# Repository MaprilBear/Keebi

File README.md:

# Keebi

Final project of ECE 445L (Embedded Systems Design Lab) at UT Austin with Mark McDermott (Fall 2023)

The Keebi is a USB and Bluetooth enabled wireless hotswappable 60% keyboard with an attached color TFT LCD

MCUs: TM4C123G and the BGM220P <br>
LCD: Adafruit 1.8" TFT LCD (Product ID 358) <br>

A bill of materials is included in this repository

## Credits
- April Douglas - Schematic and PCB Design, Firmware
- Matija Jankovic - Schematic and PCB Design, PCB Assembly
- Jenna May - Firmware
- Eric Wang - Case

## How to Use
- Fn+B - Toggle Bluetooth 
- Fn+Period - Cycle between apps 
- All keys are defined in Switch_Matrix.c

## Errata
1.  The bottom row of keys is unconnected to the main MCU
    -  Fix - Solder a wire from the bottom of the Left Arrow key diode to the TDO pin of the JTAG pinout. Holding down both shift keys will return TDO to it's JTAG confirguration and allow for flashing
2. There is crosstalk between the control, alt, shift, and windows keys in the bottom right. Win+RShift for example is detected as Ctrl+Win+RShift and Ctrl+Z is sometimes detected as Ctrl+Alt+Z
    - No Fix 
3. Bluetooth will sometimes break and cause the keyboard to become entirely unresponsive outside of the current app on the display
    - Workaround - When using bluetooth make sure to toggle the blank screen app with Fn+Period, this will avoid the crash in most situations
    - Theorized Cause - Crosstalk between LCD SPI traces and UART traces to the BGM220P or some other issue leading to malformed UART packets which the BGM220P firmware is not designed to handle

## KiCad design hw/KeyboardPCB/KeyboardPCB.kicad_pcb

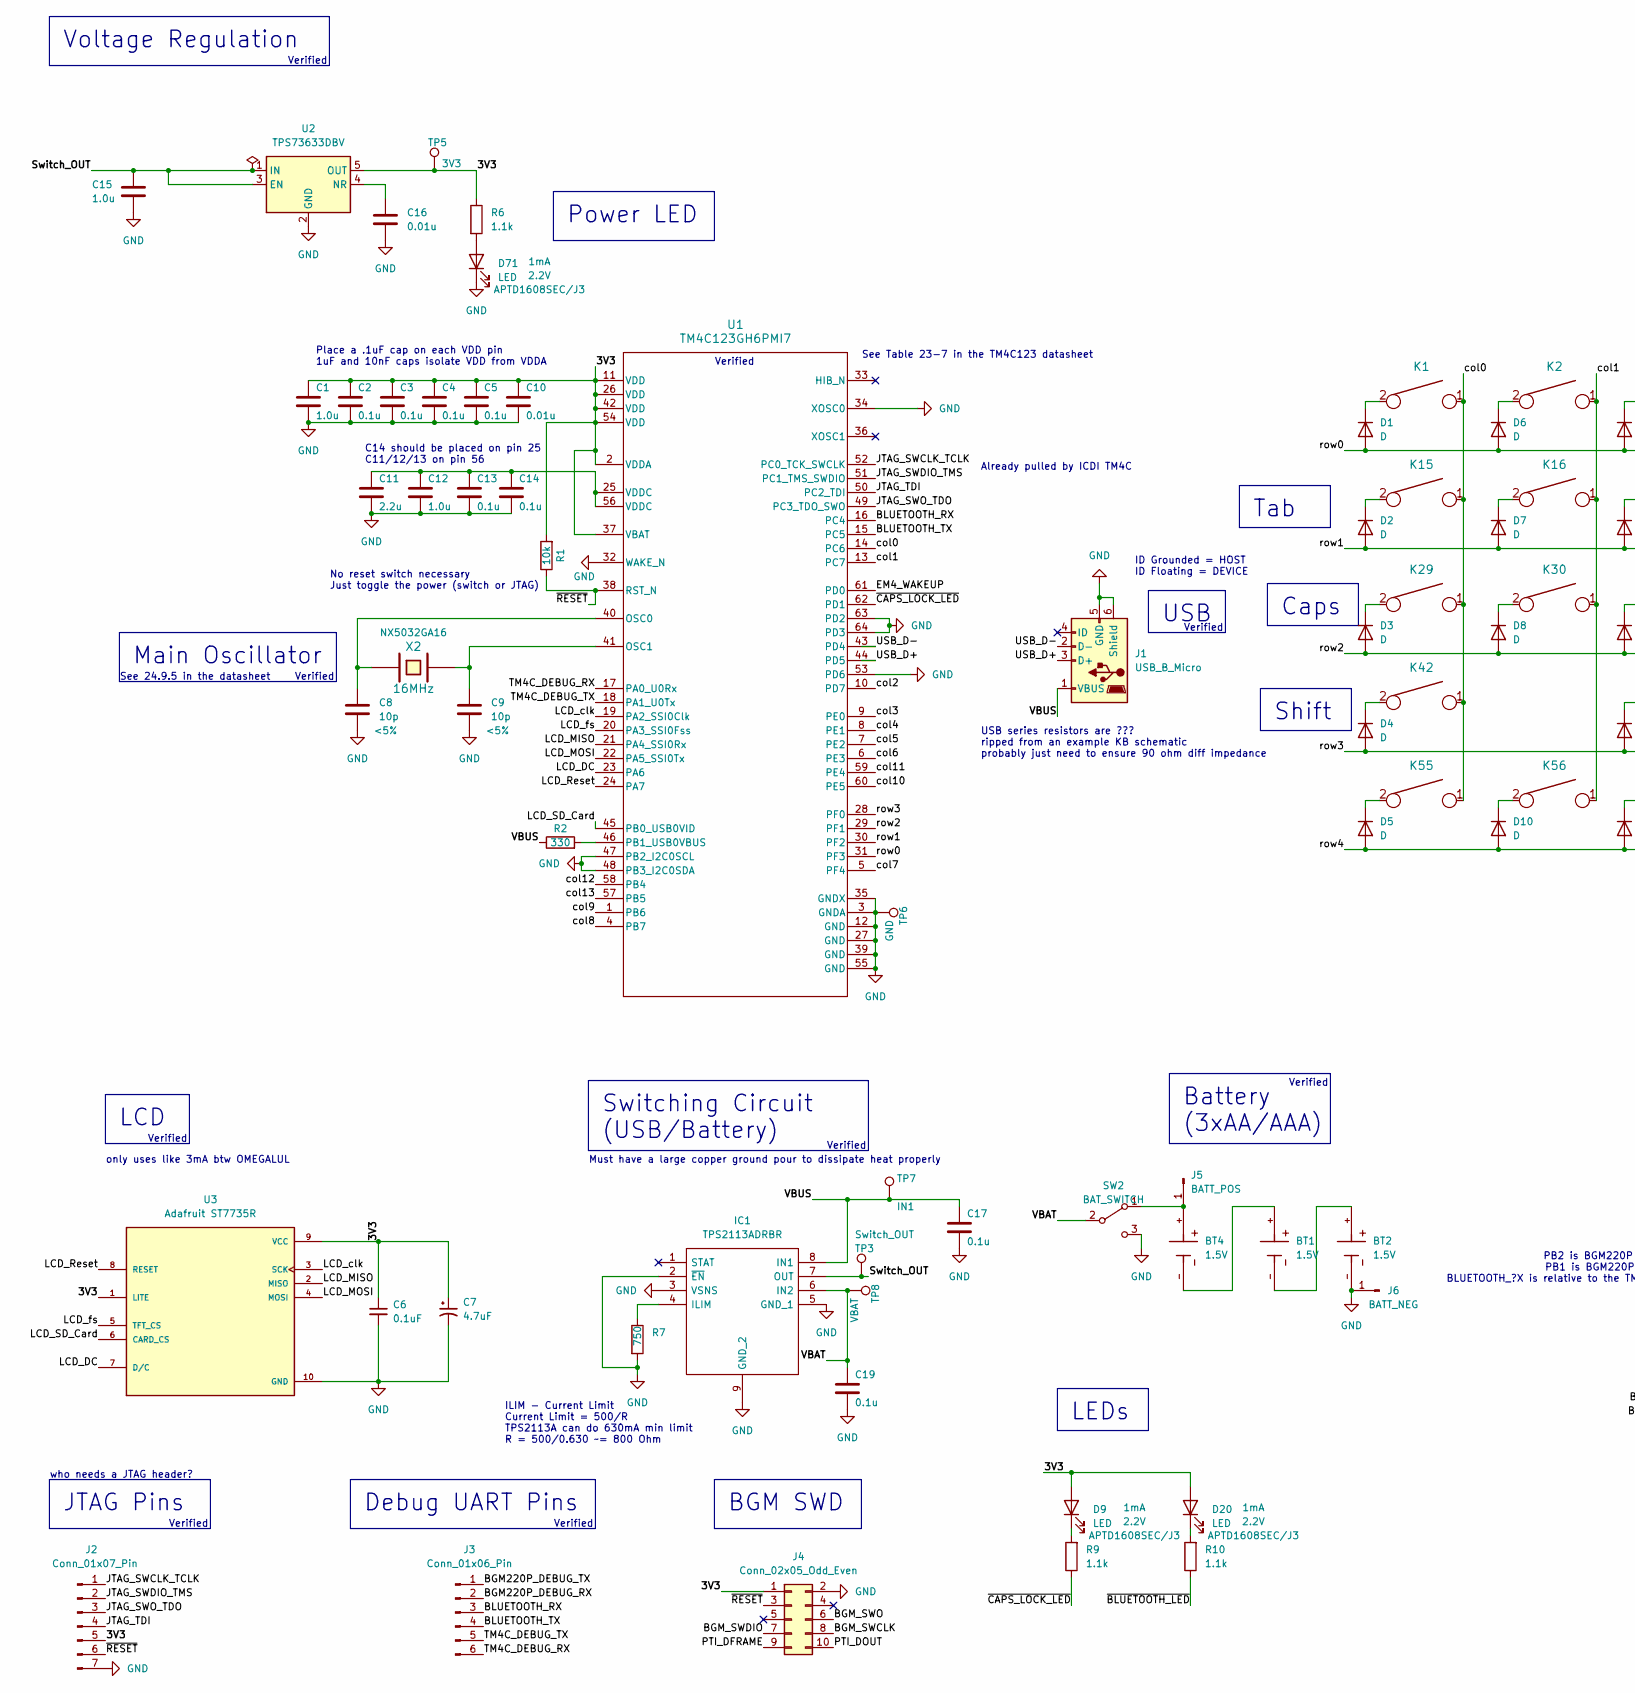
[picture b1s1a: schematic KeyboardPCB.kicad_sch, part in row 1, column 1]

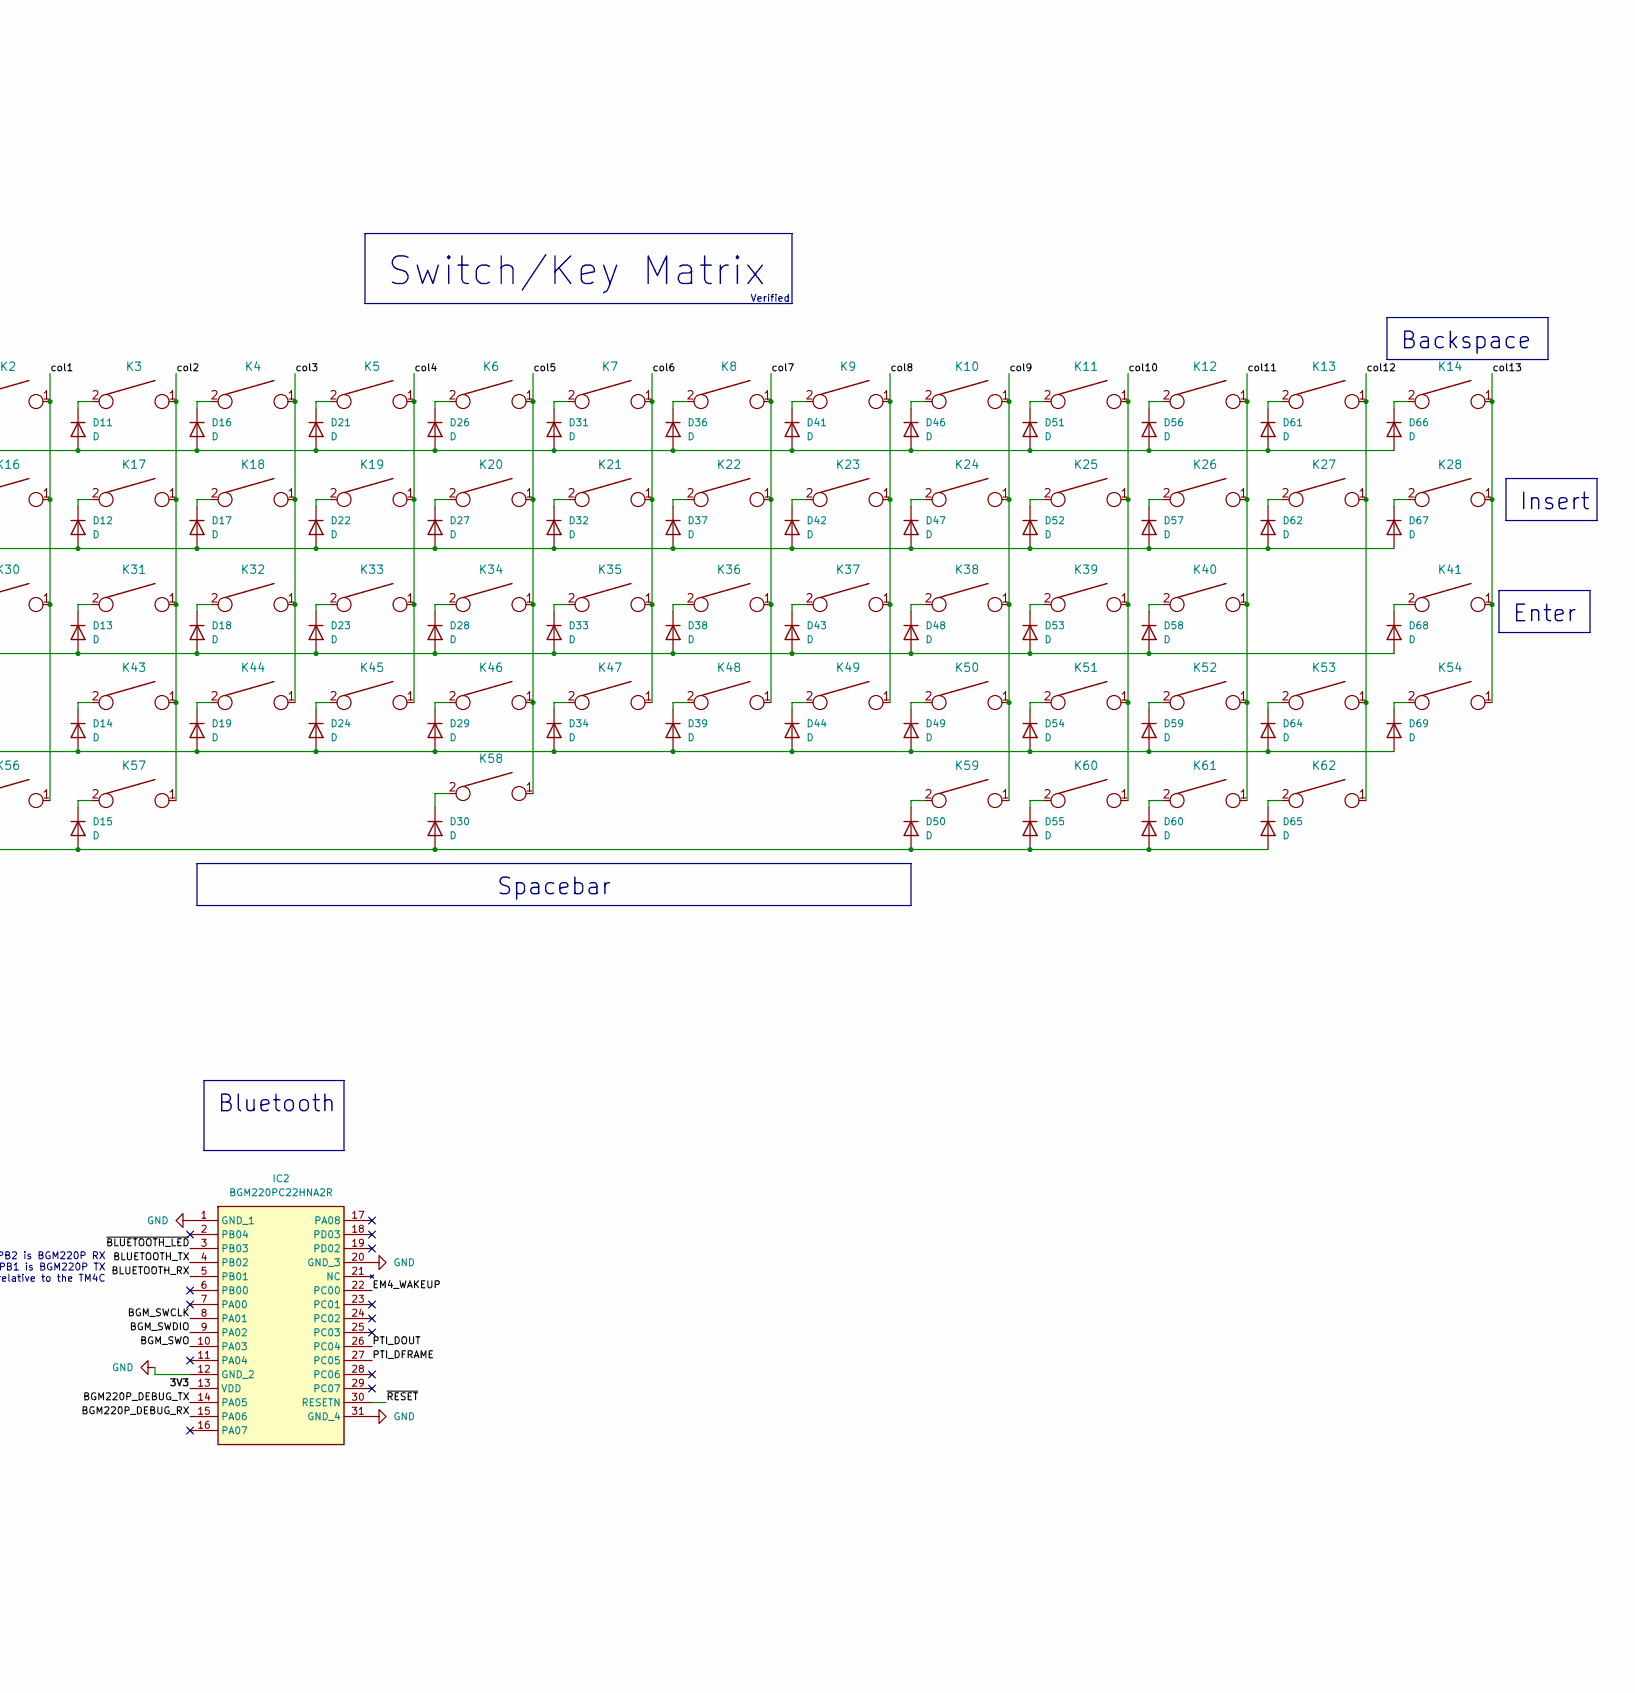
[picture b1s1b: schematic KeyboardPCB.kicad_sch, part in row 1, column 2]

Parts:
BT1, BT2, BT4: 1.5V; PARTREV A
C1, C12, C15: 1.0u; C_0603_1608Metric_Pad1.08x0.95mm_HandSolder
C2, C3, C4, C5, C13, C14, C17, C19: 0.1u; C_0603_1608Metric_Pad1.08x0.95mm_HandSolder
C6: 0.1uF; C_0603_1608Metric_Pad1.08x0.95mm_HandSolder
C7: 4.7uF; C_0603_1608Metric_Pad1.08x0.95mm_HandSolder
C8, C9: 10p; C_0603_1608Metric_Pad1.08x0.95mm_HandSolder; Tolerance <5%
C10, C16: 0.01u; C_0603_1608Metric_Pad1.08x0.95mm_HandSolder
C11: 2.2u; C_0603_1608Metric_Pad1.08x0.95mm_HandSolder
D1, D2, D3, D4, D5, D6, D7, D8, D10, D11, D12, D13, D14, D15, D16, D17, D18, D19, D21, D22, D23, D24, D26, D27, D28, D29, D30, D31, D32, D33, D34, D36, D37, D38, D39, D41, D42, D43, D44, D46, D47, D48, D49, D50, D51, D52, D53, D54, D55, D56, D57, D58, D59, D60, D61, D62, D64, D65, D66, D67, D68, D69: D; D_SOD-123
D9, D20, D71: LED; LED_0603_1608Metric_Pad1.05x0.95mm_HandSolder; Part APTD1608SEC/J3
IC1: TPS2113ADRBR; SON65P300X300X100-9N-D; Mouser Part Number 595-TPS2113ADRBR
IC2: BGM220PC22HNA2R; Mouser Part Number 634-BGM220PC22HNA2R
J1: USB_B_Micro; USB_Micro-B_Amphenol_10103594-0001LF_Horizontal
J2: Conn_01x07_Pin; PinHeader_1x07_P2.54mm_Vertical
J3: Conn_01x06_Pin; PinHeader_1x06_P2.54mm_Vertical
J4: Conn_02x05_Odd_Even; PinHeader_2x05_P1.27mm_Vertical
J5: BATT_POS; Pin_D1.0mm_L10.0mm
J6: BATT_NEG; Pin_D1.0mm_L10.0mm
K1, K2, K3, K4, K5, K6, K7, K8, K9, K10, K11, K12, K13, K16, K17, K18, K19, K20, K21, K22, K23, K24, K25, K26, K27, K30, K31, K32, K33, K34, K35, K36, K37, K38, K39, K40, K43, K44, K45, K46, K47, K48, K49, K50, K51, K52: KEYSW; MX-Hotswap-1U
K14: KEYSW; MX-Hotswap-2U
K15, K28, K53: KEYSW; MX-Hotswap-1.5U
K29: KEYSW; MX-Hotswap-1.75U
K41, K42: KEYSW; MX-Hotswap-2.25U
K54, K55, K56, K57, K59, K60, K61, K62: KEYSW; MX-Hotswap-1.25U
K58: KEYSW; MX-Hotswap-6.25U
R1: 10k; R_0402_1005Metric
R2: 330; R_0402_1005Metric
R6, R9, R10: 1.1k; R_0402_1005Metric
R7: 750; R_0402_1005Metric
SW2: BAT_SWITCH; SLW1215865AD
TP3: Switch_OUT; TestPoint_Pad_2.5x2.5mm
TP5: 3V3; TestPoint_Pad_2.5x2.5mm
TP6: GND; TestPoint_Pad_2.5x2.5mm
TP7: IN1; TestPoint_Pad_2.5x2.5mm
TP8: VBAT; TestPoint_Pad_2.5x2.5mm
U1: TM4C123GH6PMI7; QFP50P1200X1200X160-64N
U2: TPS73633DBV; SOT-23-5
U3: Adafruit ST7735R; adafruit_st7735r
X2: 16MHz; NX5032GA16000000MHZLNCD1

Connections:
/3V3: C1.1, C2.1, C3.1, C4.1, C5.1, C6.1, C7.1, C10.1, D9.2 (A), D20.2 (A), IC2.13 (VDD), J2.5, J4.1, R1.2, R6.1, TP5.1, U1.2 (VDDA), U1.11 (VDD), U1.26 (VDD), U1.37 (VBAT), U1.42 (VDD), U1.54 (VDD), U2.5 (OUT), U3.1 (LITE), U3.9 (VCC)
/BGM220P_DEBUG_RX: IC2.15 (PA06), J3.2
/BGM220P_DEBUG_TX: IC2.14 (PA05), J3.1
/BGM_SWCLK: IC2.8 (PA01), J4.8
/BGM_SWDIO: IC2.9 (PA02), J4.7
/BGM_SWO: IC2.10 (PA03), J4.6
/BLUETOOTH_RX: IC2.5 (PB01), J3.3, U1.16 (PC4)
/BLUETOOTH_TX: IC2.4 (PB02), J3.4, U1.15 (PC5)
/EM4_WAKEUP: IC2.22 (PC00), U1.61 (PD0)
/JTAG_SWCLK_TCLK: J2.1, U1.52 (PC0_TCK_SWCLK)
/JTAG_SWDIO_TMS: J2.2, U1.51 (PC1_TMS_SWDIO)
/JTAG_SWO_TDO: J2.3, U1.49 (PC3_TDO_SWO)
/JTAG_TDI: J2.4, U1.50 (PC2_TDI)
/LCD_DC: U1.23 (PA6), U3.7 (D/C)
/LCD_MISO: U1.21 (PA4_SSI0Rx), U3.2 (MISO)
/LCD_MOSI: U1.22 (PA5_SSI0Tx), U3.4 (MOSI)
/LCD_Reset: U1.24 (PA7), U3.8 (RESET)
/LCD_SD_Card: U1.45 (PB0_USB0VID), U3.6 (CARD_CS)
/LCD_clk: U1.19 (PA2_SSI0Clk), U3.3 (SCK)
/LCD_fs: U1.20 (PA3_SSI0Fss), U3.5 (TFT_CS)
/PTI_DFRAME: IC2.27 (PC05), J4.9
/PTI_DOUT: IC2.26 (PC04), J4.10
/Switch_OUT: C15.2, IC1.7 (OUT), TP3.1, U2.1 (IN), U2.3 (EN)
/TM4C_DEBUG_RX: J3.6, U1.17 (PA0_U0Rx)
/TM4C_DEBUG_TX: J3.5, U1.18 (PA1_U0Tx)
/USB_D+: J1.3 (D+), U1.44 (PD5)
/USB_D-: J1.2 (D-), U1.43 (PD4)
/VBAT: C19.1, IC1.6 (IN2), SW2.2 (B), TP8.1
/VBUS: C17.1, IC1.8 (IN1), J1.1 (VBUS), R2.1, TP7.1
/col0: K1.1, K15.1, K29.1, K42.1, K55.1, U1.14 (PC6)
/col1: K2.1, K16.1, K30.1, K56.1, U1.13 (PC7)
/col2: K3.1, K17.1, K31.1, K43.1, K57.1, U1.10 (PD7)
/col3: K4.1, K18.1, K32.1, K44.1, U1.9 (PE0)
/col4: K5.1, K19.1, K33.1, K45.1, U1.8 (PE1)
/col5: K6.1, K20.1, K34.1, K46.1, K58.1, U1.7 (PE2)
/col6: K7.1, K21.1, K35.1, K47.1, U1.6 (PE3)
/col7: K8.1, K22.1, K36.1, K48.1, U1.5 (PF4)
/col8: K9.1, K23.1, K37.1, K49.1, U1.4 (PB7)
/col9: K10.1, K24.1, K38.1, K50.1, K59.1, U1.1 (PB6)
/col10: K11.1, K25.1, K39.1, K51.1, K60.1, U1.60 (PE5)
/col11: K12.1, K26.1, K40.1, K52.1, K61.1, U1.59 (PE4)
/col12: K13.1, K27.1, K53.1, K62.1, U1.58 (PB4)
/col13: K14.1, K28.1, K41.1, K54.1, U1.57 (PB5)
/row0: D1.2 (A), D6.2 (A), D11.2 (A), D16.2 (A), D21.2 (A), D26.2 (A), D31.2 (A), D36.2 (A), D41.2 (A), D46.2 (A), D51.2 (A), D56.2 (A), D61.2 (A), D66.2 (A), U1.31 (PF3)
/row1: D2.2 (A), D7.2 (A), D12.2 (A), D17.2 (A), D22.2 (A), D27.2 (A), D32.2 (A), D37.2 (A), D42.2 (A), D47.2 (A), D52.2 (A), D57.2 (A), D62.2 (A), D67.2 (A), U1.30 (PF2)
/row2: D3.2 (A), D8.2 (A), D13.2 (A), D18.2 (A), D23.2 (A), D28.2 (A), D33.2 (A), D38.2 (A), D43.2 (A), D48.2 (A), D53.2 (A), D58.2 (A), D68.2 (A), U1.29 (PF1)
/row3: D4.2 (A), D14.2 (A), D19.2 (A), D24.2 (A), D29.2 (A), D34.2 (A), D39.2 (A), D44.2 (A), D49.2 (A), D54.2 (A), D59.2 (A), D64.2 (A), D69.2 (A), U1.28 (PF0)
/row4: D5.2 (A), D10.2 (A), D15.2 (A), D30.2 (A), D50.2 (A), D55.2 (A), D60.2 (A), D65.2 (A)
/~BLUETOOTH_LED: IC2.3 (PB03), R10.1
/~CAPS_LOCK_LED: R9.1, U1.62 (PD1)
/~RESET: IC2.30 (RESETN), J2.6, J4.3, R1.1, U1.38 (RST_N)
GND: BT2.-, C1.2, C2.2, C3.2, C4.2, C5.2, C6.2, C7.2, C8.2, C9.2, C10.2, C11.2, C12.2, C13.2, C14.2, C15.1, C16.2, C17.2, C19.2, D71.1 (K), IC1.2 (~EN), IC1.3 (VSNS), IC1.5 (GND_1), IC1.9 (GND_2), IC2.1 (GND_1), IC2.12 (GND_2), IC2.20 (GND_3), IC2.31 (GND_4), J1.5 (GND), J1.6 (Shield), J2.7, J4.2, J6.1, R7.2, SW2.3 (C), TP6.1, U1.3 (GNDA), U1.12 (GND), U1.27 (GND), U1.32 (WAKE_N), U1.34 (XOSC0), U1.35 (GNDX), U1.39 (GND), U1.47 (PB2_I2C0SCL), U1.48 (PB3_I2C0SDA), U1.53 (PD6), U1.55 (GND), U1.63 (PD2), U1.64 (PD3), U2.2 (GND), U3.10 (GND)
unnamed: BT1.+, BT4.-
unnamed: BT1.-, BT2.+
unnamed: C11.1, C12.1, C13.1, C14.1, U1.25 (VDDC), U1.56 (VDDC)
unnamed: D1.1 (K), K1.2
unnamed: D2.1 (K), K15.2
unnamed: D3.1 (K), K29.2
unnamed: D4.1 (K), K42.2
unnamed: D5.1 (K), K55.2
unnamed: D6.1 (K), K2.2
unnamed: D7.1 (K), K16.2
unnamed: D8.1 (K), K30.2
unnamed: D9.1 (K), R9.2
unnamed: D10.1 (K), K56.2
unnamed: D11.1 (K), K3.2
unnamed: D12.1 (K), K17.2
unnamed: D13.1 (K), K31.2
unnamed: D14.1 (K), K43.2
unnamed: D15.1 (K), K57.2
unnamed: D16.1 (K), K4.2
unnamed: D17.1 (K), K18.2
unnamed: D18.1 (K), K32.2
unnamed: D19.1 (K), K44.2
unnamed: D20.1 (K), R10.2
unnamed: D21.1 (K), K5.2
unnamed: D22.1 (K), K19.2
unnamed: D23.1 (K), K33.2
unnamed: D24.1 (K), K45.2
unnamed: D26.1 (K), K6.2
unnamed: D27.1 (K), K20.2
unnamed: D28.1 (K), K34.2
unnamed: D29.1 (K), K46.2
unnamed: D30.1 (K), K58.2
unnamed: D31.1 (K), K7.2
unnamed: D32.1 (K), K21.2
unnamed: D33.1 (K), K35.2
unnamed: D34.1 (K), K47.2
unnamed: D36.1 (K), K8.2
unnamed: D37.1 (K), K22.2
unnamed: D38.1 (K), K36.2
unnamed: D39.1 (K), K48.2
unnamed: D41.1 (K), K9.2
unnamed: D42.1 (K), K23.2
unnamed: D43.1 (K), K37.2
unnamed: D44.1 (K), K49.2
unnamed: D46.1 (K), K10.2
unnamed: D47.1 (K), K24.2
unnamed: D48.1 (K), K38.2
unnamed: D49.1 (K), K50.2
unnamed: D50.1 (K), K59.2
unnamed: D51.1 (K), K11.2
unnamed: D52.1 (K), K25.2
unnamed: D53.1 (K), K39.2
unnamed: D54.1 (K), K51.2
unnamed: D55.1 (K), K60.2
unnamed: D56.1 (K), K12.2
unnamed: D57.1 (K), K26.2
unnamed: D58.1 (K), K40.2
unnamed: D59.1 (K), K52.2
unnamed: D60.1 (K), K61.2
unnamed: D61.1 (K), K13.2
unnamed: D62.1 (K), K27.2
unnamed: D64.1 (K), K53.2
unnamed: D65.1 (K), K62.2
unnamed: D66.1 (K), K14.2
unnamed: D67.1 (K), K28.2
unnamed: D68.1 (K), K41.2
unnamed: D69.1 (K), K54.2
unnamed: D71.2 (A), R6.2
unnamed: IC1.4 (ILIM), R7.1
unnamed: BT4.+, J5.1, SW2.1 (A)
unnamed: C8.1, U1.40 (OSC0), X2.1
unnamed: C9.1, U1.41 (OSC1), X2.2
unnamed: R2.2, U1.46 (PB1_USB0VBUS)
unnamed: C16.1, U2.4 (NR)

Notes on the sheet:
Shift
Main Oscillator
Caps
JTAG Pins
Bluetooth
USB
LCD
Insert
Voltage Regulation
Backspace
Switch/Key Matrix
Tab
Enter
BGM SWD
Battery (3xAA/AAA)
Debug UART Pins
Switching Circuit (USB/Battery)
Spacebar
Power LED
LEDs
See 24.9.5 in the datasheet
Verified
Already pulled by ICDI TM4C
C14 should be placed on pin 25 C11/12/13 on pin 56
only uses like 3mA btw OMEGALUL
No reset switch necessary Just toggle the power (switch or JTAG)
Place a .1uF cap on each VDD pin 1uF and 10nF caps isolate VDD from VDDA
ILIM - Current Limit Current Limit = 500/R TPS2113A can do 630mA min limit R = 500/0.630 ~= 800 Ohm
who needs a JTAG header?
ID Grounded = HOST ID Floating = DEVICE
USB series resistors are ??? ripped from an example KB schematic probably just need to ensure 90 ohm diff impedance
PB2 is BGM220P RX PB1 is BGM220P TX BLUETOOTH_?X is relative to the TM4C
See Table 23-7 in the TM4C123 datasheet
Must have a large copper ground pour to dissipate heat properly

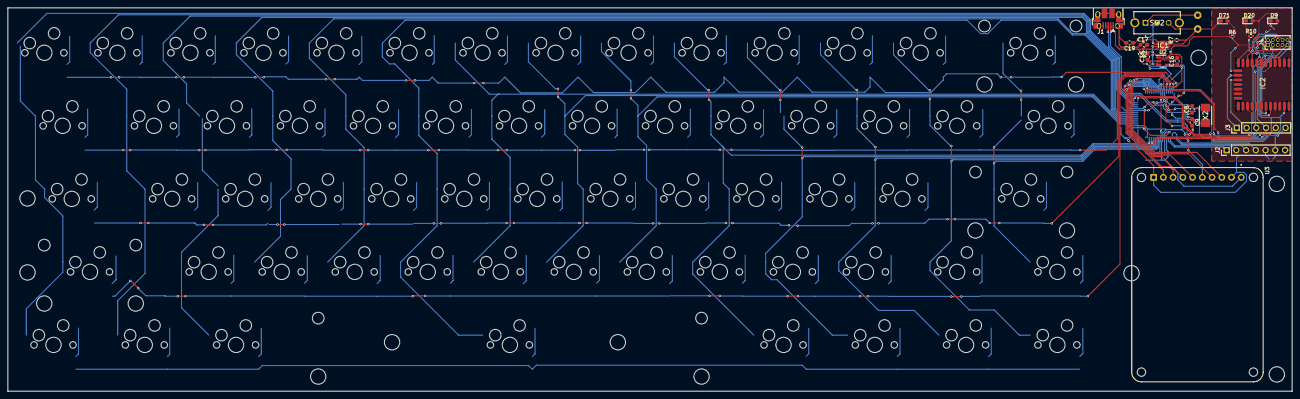
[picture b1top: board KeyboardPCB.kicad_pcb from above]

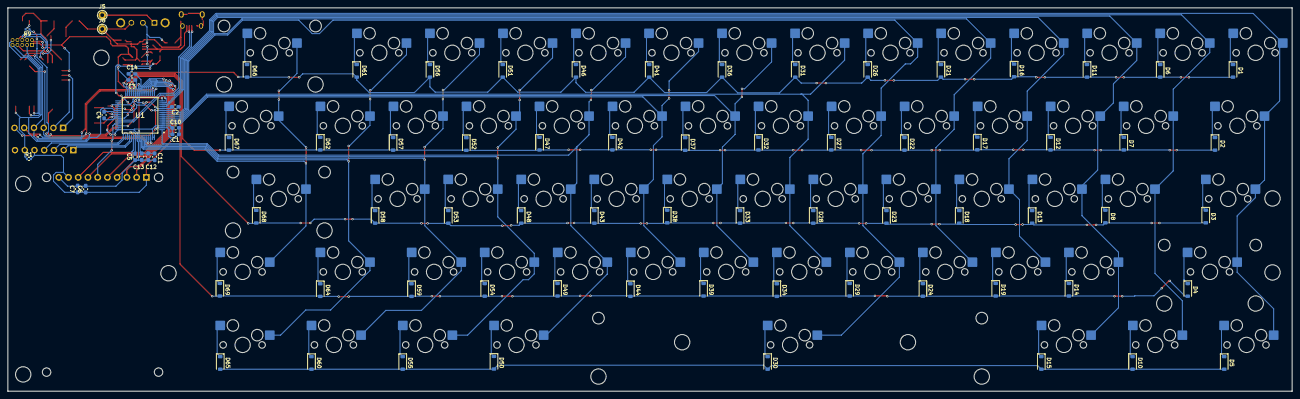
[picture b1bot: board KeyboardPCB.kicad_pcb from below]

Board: 2 copper layers, 335.0 x 100.0 mm, 164 parts (79 on the bottom side), 124 nets.

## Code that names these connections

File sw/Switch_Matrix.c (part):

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#include "Keyboard.h"
#include <stdbool.h>

#define ROW0 PF3
#define ROW1 PF2
#define ROW2 PF1
#define ROW3 PF0
#define ROW4 PC3 // TDO, must unlock


#define COL0 PC6
#define COL1 PC7
#define COL2 PD7
#define COL3 PE0
#define COL4 PE1
#define COL5 PE2
#define COL6 PE3
#define COL7 PF4
#define COL8 PB7
#define COL9 PB6
#define COL10 PE5
#define COL11 PE4
#define COL12 PB4
#define COL13 PB5

uint8_t modifier = 0;

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  
	
    
      // ROW0 - PF3
			
			// pulse row
			GPIO_PORTF_DATA_R |= (1 << 3);
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      
      Clock_Delay1ms(DELAY);
      
      // ROW1 - PF1
			
			// pulse row
			GPIO_PORTF_DATA_R |= (1 << 1);
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		GPIO_PORTF_DATA_R &= ~(1<<1);
      Clock_Delay1ms(DELAY);

      // ROW2 - PF2
			
			// pulse row
			GPIO_PORTF_DATA_R |= (1 << 2);
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      GPIO_PORTF_DATA_R &= ~(1 << 2);
      Clock_Delay1ms(DELAY);

      // ROW3 - PF0
			
			// pulse row
			GPIO_PORTF_DATA_R |= (1 << 0);
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      GPIO_PORTF_DATA_R &= ~(1 << 0);
      Clock_Delay1ms(DELAY);
                    
      // ROW4 - PC3
			
			// pulse row
			GPIO_PORTC_DATA_R |= (1 << 3);
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  
}

#define ROW0 PF3
#define ROW1 PF2
#define ROW2 PF1
#define ROW3 PF0
#define ROW4 PC3 // TDO, must unlock

void Switch_Init(){

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  GPIO_PORTF_DR8R_R |= (1 << 0) + (1 << 1) + (1 << 2) + (1 << 3);
  GPIO_PORTF_PUR_R &= ~((1 << 0) + (1 << 1) + (1 << 2) + (1 << 3));
  GPIO_PORTF_PDR_R &= ~((1 << 0) + (1 << 1) + (1 << 2) + (1 << 3));
  GPIO_PORTF_DIR_R &= ~(1 << 4); // set col7 to IN
  GPIO_PORTF_PDR_R |= (1 << 4);
	GPIO_PORTF_DEN_R |= 1 + (1 << 1) + (1 << 2) + (1<<3) + (1 << 4);
	
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
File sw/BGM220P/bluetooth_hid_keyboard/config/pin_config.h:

#ifndef PIN_CONFIG_H
#define PIN_CONFIG_H

// $[CMU]
// [CMU]$

// $[PRS.ASYNCH0]
// [PRS.ASYNCH0]$

// $[PRS.ASYNCH1]
// [PRS.ASYNCH1]$

// $[PRS.ASYNCH2]
// [PRS.ASYNCH2]$

// $[PRS.ASYNCH3]
// [PRS.ASYNCH3]$

// $[PRS.ASYNCH4]
// [PRS.ASYNCH4]$

// $[PRS.ASYNCH5]
// [PRS.ASYNCH5]$

// $[PRS.ASYNCH6]
// [PRS.ASYNCH6]$

// $[PRS.ASYNCH7]
// [PRS.ASYNCH7]$

// $[PRS.ASYNCH8]
// [PRS.ASYNCH8]$

// $[PRS.ASYNCH9]
// [PRS.ASYNCH9]$

// $[PRS.ASYNCH10]
// [PRS.ASYNCH10]$

// $[PRS.ASYNCH11]
// [PRS.ASYNCH11]$

// $[PRS.SYNCH0]
// [PRS.SYNCH0]$

// $[PRS.SYNCH1]
// [PRS.SYNCH1]$

// $[PRS.SYNCH2]
// [PRS.SYNCH2]$

// $[PRS.SYNCH3]
// [PRS.SYNCH3]$

// $[GPIO]
// GPIO SWV on PA03
#ifndef GPIO_SWV_PORT                           
#define GPIO_SWV_PORT                            gpioPortA
#endif
#ifndef GPIO_SWV_PIN                            
#define GPIO_SWV_PIN                             3
#endif

// [GPIO]$

// $[TIMER0]
// [TIMER0]$

// $[TIMER1]
// [TIMER1]$

// $[TIMER2]
// [TIMER2]$

// $[TIMER3]
// [TIMER3]$

// $[TIMER4]
// [TIMER4]$

// $[USART0]
// USART0 RX on PA06
#ifndef USART0_RX_PORT                          
#define USART0_RX_PORT                           gpioPortA
#endif
#ifndef USART0_RX_PIN                           
#define USART0_RX_PIN                            6
#endif

// USART0 TX on PA05
#ifndef USART0_TX_PORT                          
#define USART0_TX_PORT                           gpioPortA
#endif
#ifndef USART0_TX_PIN                           
#define USART0_TX_PIN                            5
#endif

// [USART0]$

// $[USART1]
// USART1 RX on PB02
#ifndef USART1_RX_PORT                          
#define USART1_RX_PORT                           gpioPortB
#endif
#ifndef USART1_RX_PIN                           
#define USART1_RX_PIN                            2
#endif

// USART1 TX on PB01
#ifndef USART1_TX_PORT                          
#define USART1_TX_PORT                           gpioPortB
#endif
#ifndef USART1_TX_PIN                           
#define USART1_TX_PIN                            1
#endif

// [USART1]$

// $[I2C1]
// [I2C1]$

// $[PDM]
// [PDM]$

// $[LETIMER0]
// [LETIMER0]$

// $[IADC0]
// [IADC0]$

// $[I2C0]
// [I2C0]$

// $[EUART0]
// [EUART0]$

// $[PTI]
// PTI DFRAME on PC05
#ifndef PTI_DFRAME_PORT                         
#define PTI_DFRAME_PORT                          gpioPortC
#endif
#ifndef PTI_DFRAME_PIN                          
#define PTI_DFRAME_PIN                           5
#endif

// PTI DOUT on PC04
#ifndef PTI_DOUT_PORT                           
#define PTI_DOUT_PORT                            gpioPortC
#endif
#ifndef PTI_DOUT_PIN                            
#define PTI_DOUT_PIN                             4
#endif

// [PTI]$

// $[MODEM]
// [MODEM]$

// $[CUSTOM_PIN_NAME]
#ifndef STATUS_LED_PORT                         
#define STATUS_LED_PORT                          gpioPortB
#endif
#ifndef STATUS_LED_PIN                          
#define STATUS_LED_PIN                           3
#endif

// [CUSTOM_PIN_NAME]$

#endif // PIN_CONFIG_H

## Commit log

2023-10-12 GitHub Classroom Feedback
2023-10-12 Setting up GitHub Classroom Feedback
2023-10-12 add online IDE url
2023-10-18 Initial USB Keyboard Example
2023-10-20 added requirements doc
2023-10-20 Added PCB files, updated requirements doc, and submitted rough draft lab7 doc.
2023-10-21 Initial USB and Bluetooth projects
2023-10-21 why no worky
2023-10-21 wack
2023-10-21 if only my tm4c's micro port wasn't borked
2023-10-21 small cleanup
2023-10-24 Simplicity Studio Project Fixing
2023-10-24 Getting started on UART
2023-10-24 doot doot
2023-10-24 Made updates to schematic
2023-10-25 THEY'RE TALKING!!!
2023-10-25 LCD stuff
2023-10-26 PCB update
2023-10-28 Added remaining footprints and aligned keys on layout
2023-10-28 Wrote lab 7 report
2023-10-28 Placed a few more components under keys
2023-10-28 Updated lab report with current estimations
2023-10-28 Made outline and placed all components in position. Just need to route :)
2023-10-28 Verified regulator circuit, added LEDs based on BOM
2023-10-28 Verified TM4C pin #s and important pins, MOSC, and caps
2023-10-29 Verified LCD, power mux, JTAG, USB, and switch matrix
    Also changed the switch matrix to use hotswap footprints
2023-10-29 Pray to your ECE god of choice
2023-10-30 6 traces to go :)
2023-10-30 Slight tweaks
2023-10-30 Routed up remaining traces
2023-10-30 Added EM4_WAKEUP signal from PD0 (TM4C) to PC0 (BGM)
2023-10-30 pushing the backups that were created cause I'm so used to hitting ctrl+s :/
2023-10-31 Updated BoM to include LEDs and M2x4 mounting screws.
    Length of screws can be updated depending on the thickness of the PCB
    Also updated resistor values based on forward voltage of SMD LEDs
2023-11-02 PCB done!
2023-11-03 added some basic unit testing procedures (for lab 8 report) for once pcb arrives
2023-11-04 Accidentally deleted final PCB, oops
    Old version from before last minute tuesday edits
2023-11-10 Working on USB HID keyboard firmware
2023-11-10 Routed row4 to JTAG_TDO
2023-11-15 temp
2023-11-15 temp 2
2023-11-15 more USB stuff
2023-11-16 omg keyboard!
2023-11-16 Undo what i did that makes it not work on all devices
2023-11-17 Made ESC default and fixed CAPS_LOCK
2023-11-17 Bluetooth works!
2023-11-18 Added Bluetooth Toggling
    FN+B will toggle the bluetooth mode on or off. When off it will tell the BGM220P to shutdown and when on it will wake it up.
2023-11-20 Slightly fixed ctrl/lshift/win/alt ghosting, removed redundant reports
2023-11-20 The World's Shittiest Operating System!
2023-11-27 Compressed The Bongos
2023-11-27 transferred tested bongo cat and char per min
2023-11-28 numbers change color
2023-11-28 Auto stash before merge of "main" and "origin/main"
2023-12-01 Final Code :)
2023-12-02 Updated some testing steps
2023-12-02 BOM Update
2023-12-02 Cleanup and updated README
2023-12-02 More Cleanup
2023-12-02 Added picture
2024-08-12 Rename and updated description
2024-08-12 Changed pic name
2024-08-15 Rename Keebi PCB.png to KeebiPCB.png
